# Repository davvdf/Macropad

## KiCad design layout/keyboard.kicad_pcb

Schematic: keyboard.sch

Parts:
C8: 1u; C_0805_2012Metric_Pad1.15x1.40mm_HandSolder
D_1, D_2, D_3, D_4, D_5, D_6, D_7, D_8, D_9, D_10, D_11: D; D_SOD123_axial
D_A: D; D_SOD123_axial
D_ALT: D; D_SOD123_axial
D_ASTRK: D; D_SOD123_axial
D_CAPS: D; D_SOD123_axial
D_CTRL: D; D_SOD123_axial
D_DOT: D; D_SOD123_axial
D_ENTER: D; D_SOD123_axial
D_ESC: D; D_SOD123_axial
D_L1, D_L2: D; D_SOD123_axial
D_MINUS: D; D_SOD123_axial
D_NUM: D; D_SOD123_axial
D_PLUS: D; D_SOD123_axial
D_Q: D; D_SOD123_axial
D_S: D; D_SOD123_axial
D_SHIFT: D; D_SOD123_axial
D_SLASH: D; D_SOD123_axial
D_SPACE, D_SPACE1, D_SPACE2, D_SPACE3, D_SPACE4, D_SPACE5, D_SPACE6, D_SPACE7, D_SPACE8: D; D_SOD123_axial
D_TAB: D; D_SOD123_axial
D_W: D; D_SOD123_axial
D_X: D; D_SOD123_axial
D_Z: D; D_SOD123_axial
D_`: D; D_SOD123_axial
J1: USB_mini_micro_B; USB_miniB_hirose_5S8
K_1, K_2, K_3, K_4, K_5, K_6, K_7, K_8, K_9, K_10, K_11: KEYSW; MX-1U-NoLED
K_A: KEYSW; MX-1U-NoLED
K_ALT: KEYSW; MX-1U-NoLED
K_ASTRK: KEYSW; MX-1U-NoLED
K_CAPS: KEYSW; MX-2U-NoLED
K_CTRL: KEYSW; MX-1U-NoLED
K_DOT: KEYSW; MX-1U-NoLED
K_ENTER: KEYSW; MX-1U-NoLED
K_ESC: KEYSW; MX-1U-NoLED
K_L1, K_L2: KEYSW; MX-1U-NoLED
K_MINUS: KEYSW; MX-1U-NoLED
K_NUM: KEYSW; MX-1U-NoLED
K_PLUS: KEYSW; MX-1U-NoLED
K_Q: KEYSW; MX-1U-NoLED
K_S: KEYSW; MX-1U-NoLED
K_SHIFT: KEYSW; MX-2U-NoLED
K_SLASH: KEYSW; MX-1U-NoLED
K_SPACE, K_SPACE1, K_SPACE2, K_SPACE3, K_SPACE4, K_SPACE5, K_SPACE6, K_SPACE7: KEYSW; MX-1U-NoLED
K_SPACE8: KEYSW; MX-2U-NoLED
K_TAB: KEYSW; MX-2U-NoLED
K_W: KEYSW; MX-1U-NoLED
K_X: KEYSW; MX-1U-NoLED
K_Z: KEYSW; MX-1U-NoLED
K_`: KEYSW; MX-1U-NoLED
R3: 22; R_0805_2012Metric_Pad1.15x1.40mm_HandSolder
U1: ATMEGA32U4; TQFP-44_10x10mm_P0.8mm

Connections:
/col0: K_CTRL.1, K_ESC.1, K_`.1, U1.30
/col1: K_ALT.1, K_CAPS.1, K_SHIFT.1, K_SPACE.1, K_SPACE7.1, K_TAB.1, U1.12
/col2: K_1.1, K_A.1, K_L1.1, K_Q.1, K_SPACE1.1, K_Z.1, U1.31
/col3: K_2.1, K_L2.1, K_S.1, K_SPACE2.1, K_W.1, K_X.1, U1.32
/col4: K_3.1, K_4.1, K_7.1, K_NUM.1, K_SPACE3.1, U1.18
/col5: K_5.1, K_8.1, K_10.1, K_SLASH.1, K_SPACE4.1, K_SPACE8.1, U1.19
/col6: K_6.1, K_9.1, K_11.1, K_ASTRK.1, K_DOT.1, K_SPACE5.1, U1.20
/col7: K_ENTER.1, K_MINUS.1, K_PLUS.1, K_SPACE6.1, U1.21
/row0: D_ESC.1 (K), D_SPACE.1 (K), D_SPACE1.1 (K), D_SPACE2.1 (K), D_SPACE3.1 (K), D_SPACE4.1 (K), D_SPACE5.1 (K), D_SPACE6.1 (K), U1.8
/row1: D_1.1 (K), D_2.1 (K), D_ASTRK.1 (K), D_MINUS.1 (K), D_NUM.1 (K), D_SLASH.1 (K), D_SPACE7.1 (K), D_`.1 (K), U1.9
/row2: D_7.1 (K), D_8.1 (K), D_9.1 (K), D_Q.1 (K), D_TAB.1 (K), D_W.1 (K), U1.10
/row3: D_4.1 (K), D_5.1 (K), D_6.1 (K), D_A.1 (K), D_CAPS.1 (K), D_PLUS.1 (K), D_S.1 (K), U1.11
/row4: D_3.1 (K), D_10.1 (K), D_11.1 (K), D_SHIFT.1 (K), D_X.1 (K), D_Z.1 (K), U1.28
/row5: D_ALT.1 (K), D_CTRL.1 (K), D_DOT.1 (K), D_ENTER.1 (K), D_L1.1 (K), D_L2.1 (K), D_SPACE8.1 (K), U1.29
GND: U1.5, U1.15, U1.23; also elsewhere on the board
unnamed 15: U1.16; also elsewhere on the board
unnamed 16: U1.17; also elsewhere on the board
unnamed 17: U1.6; also elsewhere on the board
unnamed: D_1.2 (A), K_1.2
unnamed: D_2.2 (A), K_2.2
unnamed: D_3.2 (A), K_3.2
unnamed: D_4.2 (A), K_4.2
unnamed: D_5.2 (A), K_5.2
unnamed: D_6.2 (A), K_6.2
unnamed: D_7.2 (A), K_7.2
unnamed: D_8.2 (A), K_8.2
unnamed: D_9.2 (A), K_9.2
unnamed: D_10.2 (A), K_10.2
unnamed: D_11.2 (A), K_11.2
unnamed: D_A.2 (A), K_A.2
unnamed: D_ALT.2 (A), K_ALT.2
unnamed: D_ASTRK.2 (A), K_ASTRK.2
unnamed: D_CAPS.2 (A), K_CAPS.2
unnamed: D_CTRL.2 (A), K_CTRL.2
unnamed: D_DOT.2 (A), K_DOT.2
unnamed: D_ENTER.2 (A), K_ENTER.2
unnamed: D_ESC.2 (A), K_ESC.2
unnamed: D_L1.2 (A), K_L1.2
unnamed: D_L2.2 (A), K_L2.2
unnamed: D_MINUS.2 (A), K_MINUS.2
unnamed: D_NUM.2 (A), K_NUM.2
unnamed: D_PLUS.2 (A), K_PLUS.2
unnamed: D_Q.2 (A), K_Q.2
unnamed: D_S.2 (A), K_S.2
unnamed: D_SHIFT.2 (A), K_SHIFT.2
unnamed: D_SLASH.2 (A), K_SLASH.2
unnamed: D_SPACE1.2 (A), K_SPACE1.2
unnamed: D_SPACE2.2 (A), K_SPACE2.2
unnamed: D_SPACE3.2 (A), K_SPACE3.2
unnamed: D_SPACE4.2 (A), K_SPACE4.2
unnamed: D_SPACE5.2 (A), K_SPACE5.2
unnamed: D_SPACE6.2 (A), K_SPACE6.2
unnamed: D_SPACE7.2 (A), K_SPACE7.2
unnamed: D_SPACE8.2 (A), K_SPACE8.2
unnamed: D_SPACE.2 (A), K_SPACE.2
unnamed: D_TAB.2 (A), K_TAB.2
unnamed: D_W.2 (A), K_W.2
unnamed: D_X.2 (A), K_X.2
unnamed: D_Z.2 (A), K_Z.2
unnamed: D_`.2 (A), K_`.2
unnamed 60: U1.13; also elsewhere on the board
unnamed 61: U1.33; also elsewhere on the board
unnamed: R3.1, U1.3
unnamed 63: U1.4; also elsewhere on the board
unnamed 80: R3.2; also elsewhere on the board
VCC: U1.2, U1.14, U1.24; also elsewhere on the board

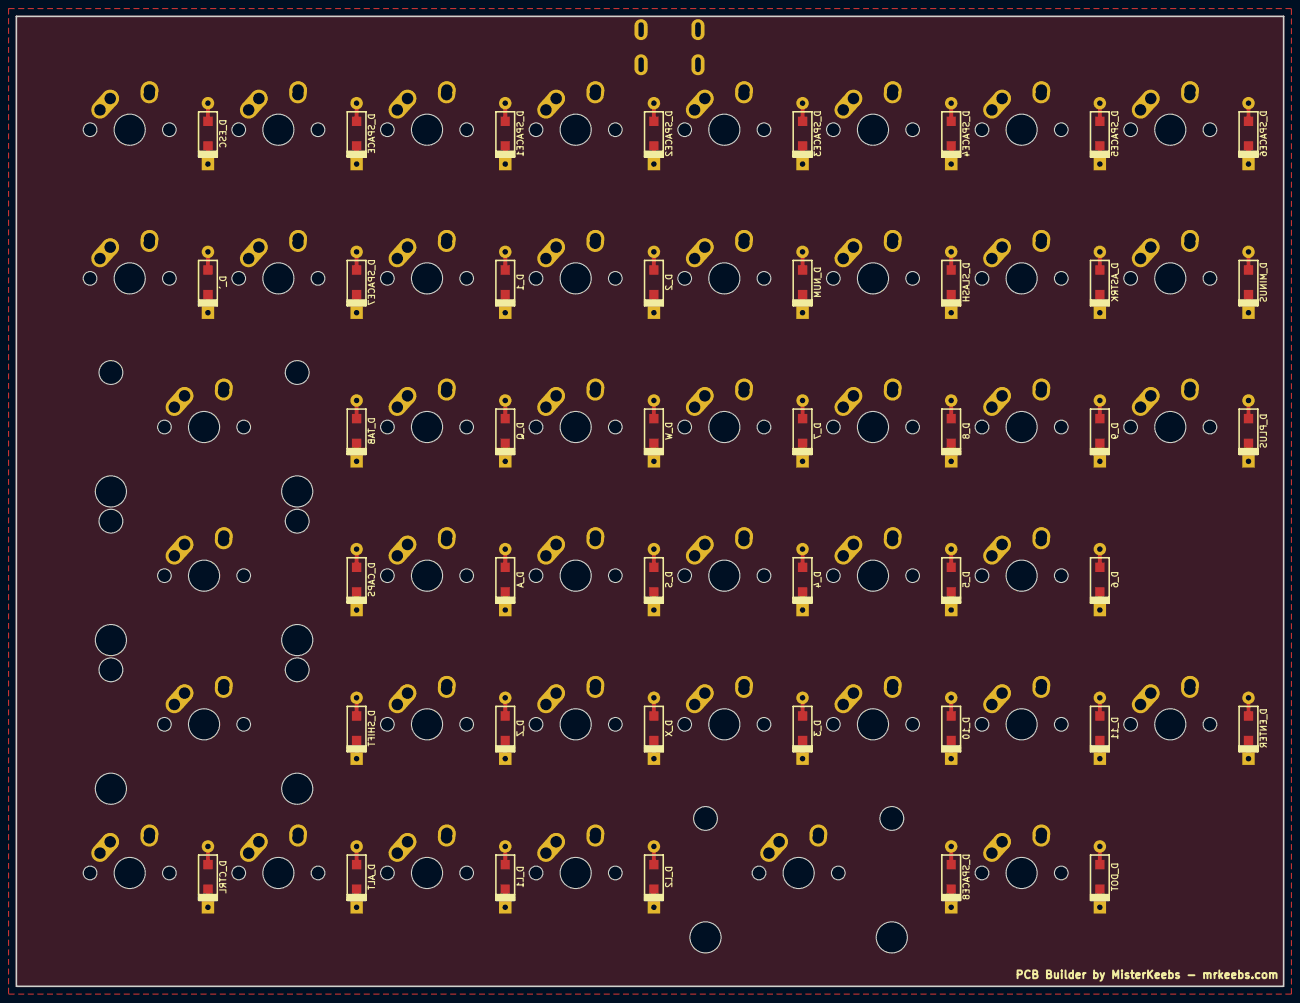
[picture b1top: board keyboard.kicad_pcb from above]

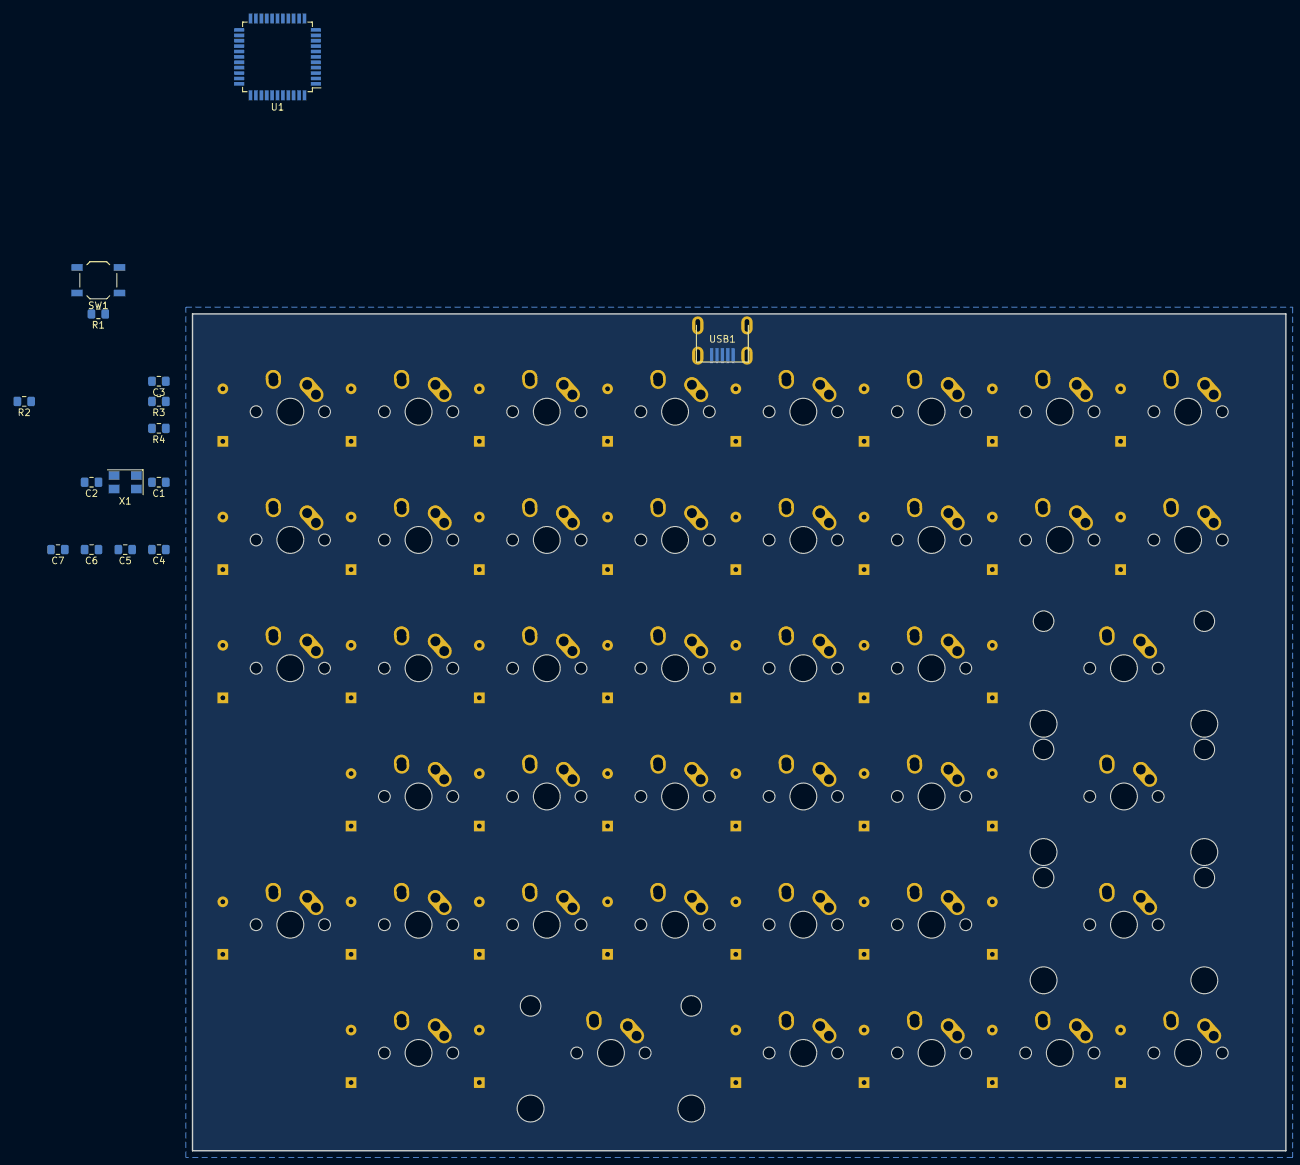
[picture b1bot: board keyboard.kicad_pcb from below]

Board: 2 copper layers, 162.4 x 124.3 mm, 99 parts (15 on the bottom side), 67 nets, no tracks yet.

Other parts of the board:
C1, C2, C3, C4, C5, C6, C7: 22pF; C_0805_2012Metric_Pad1.15x1.40mm_HandSolder
R1, R2: 10k; R_0805_2012Metric_Pad1.15x1.40mm_HandSolder
R4: 22; R_0805_2012Metric_Pad1.15x1.40mm_HandSolder
SW1: SW_PUSH; SW_SPST_TL3342
USB1: Molex-0548190589; Molex-0548190589-Assembly
X1: XTAL_GND; Crystal_SMD_5032-4Pin_5.0x3.2mm

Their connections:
GND: C1.2, C2.2, C3.2, C4.2, C5.2, C6.2, C7.2, R2.2, SW1.1, USB1.1, X1.2, X1.4; also elsewhere on the board
unnamed 15: C1.1, X1.1; also elsewhere on the board
unnamed 16: C2.1, X1.3; also elsewhere on the board
unnamed 17: C3.1; also elsewhere on the board
unnamed 60: R1.1, SW1.2; also elsewhere on the board
unnamed 61: R2.1; also elsewhere on the board
unnamed 63: R4.1; also elsewhere on the board
unnamed 80: USB1.2; also elsewhere on the board
unnamed: R4.2, USB1.3
VCC: C4.1, C5.1, C6.1, C7.1, R1.2, USB1.5; also elsewhere on the board

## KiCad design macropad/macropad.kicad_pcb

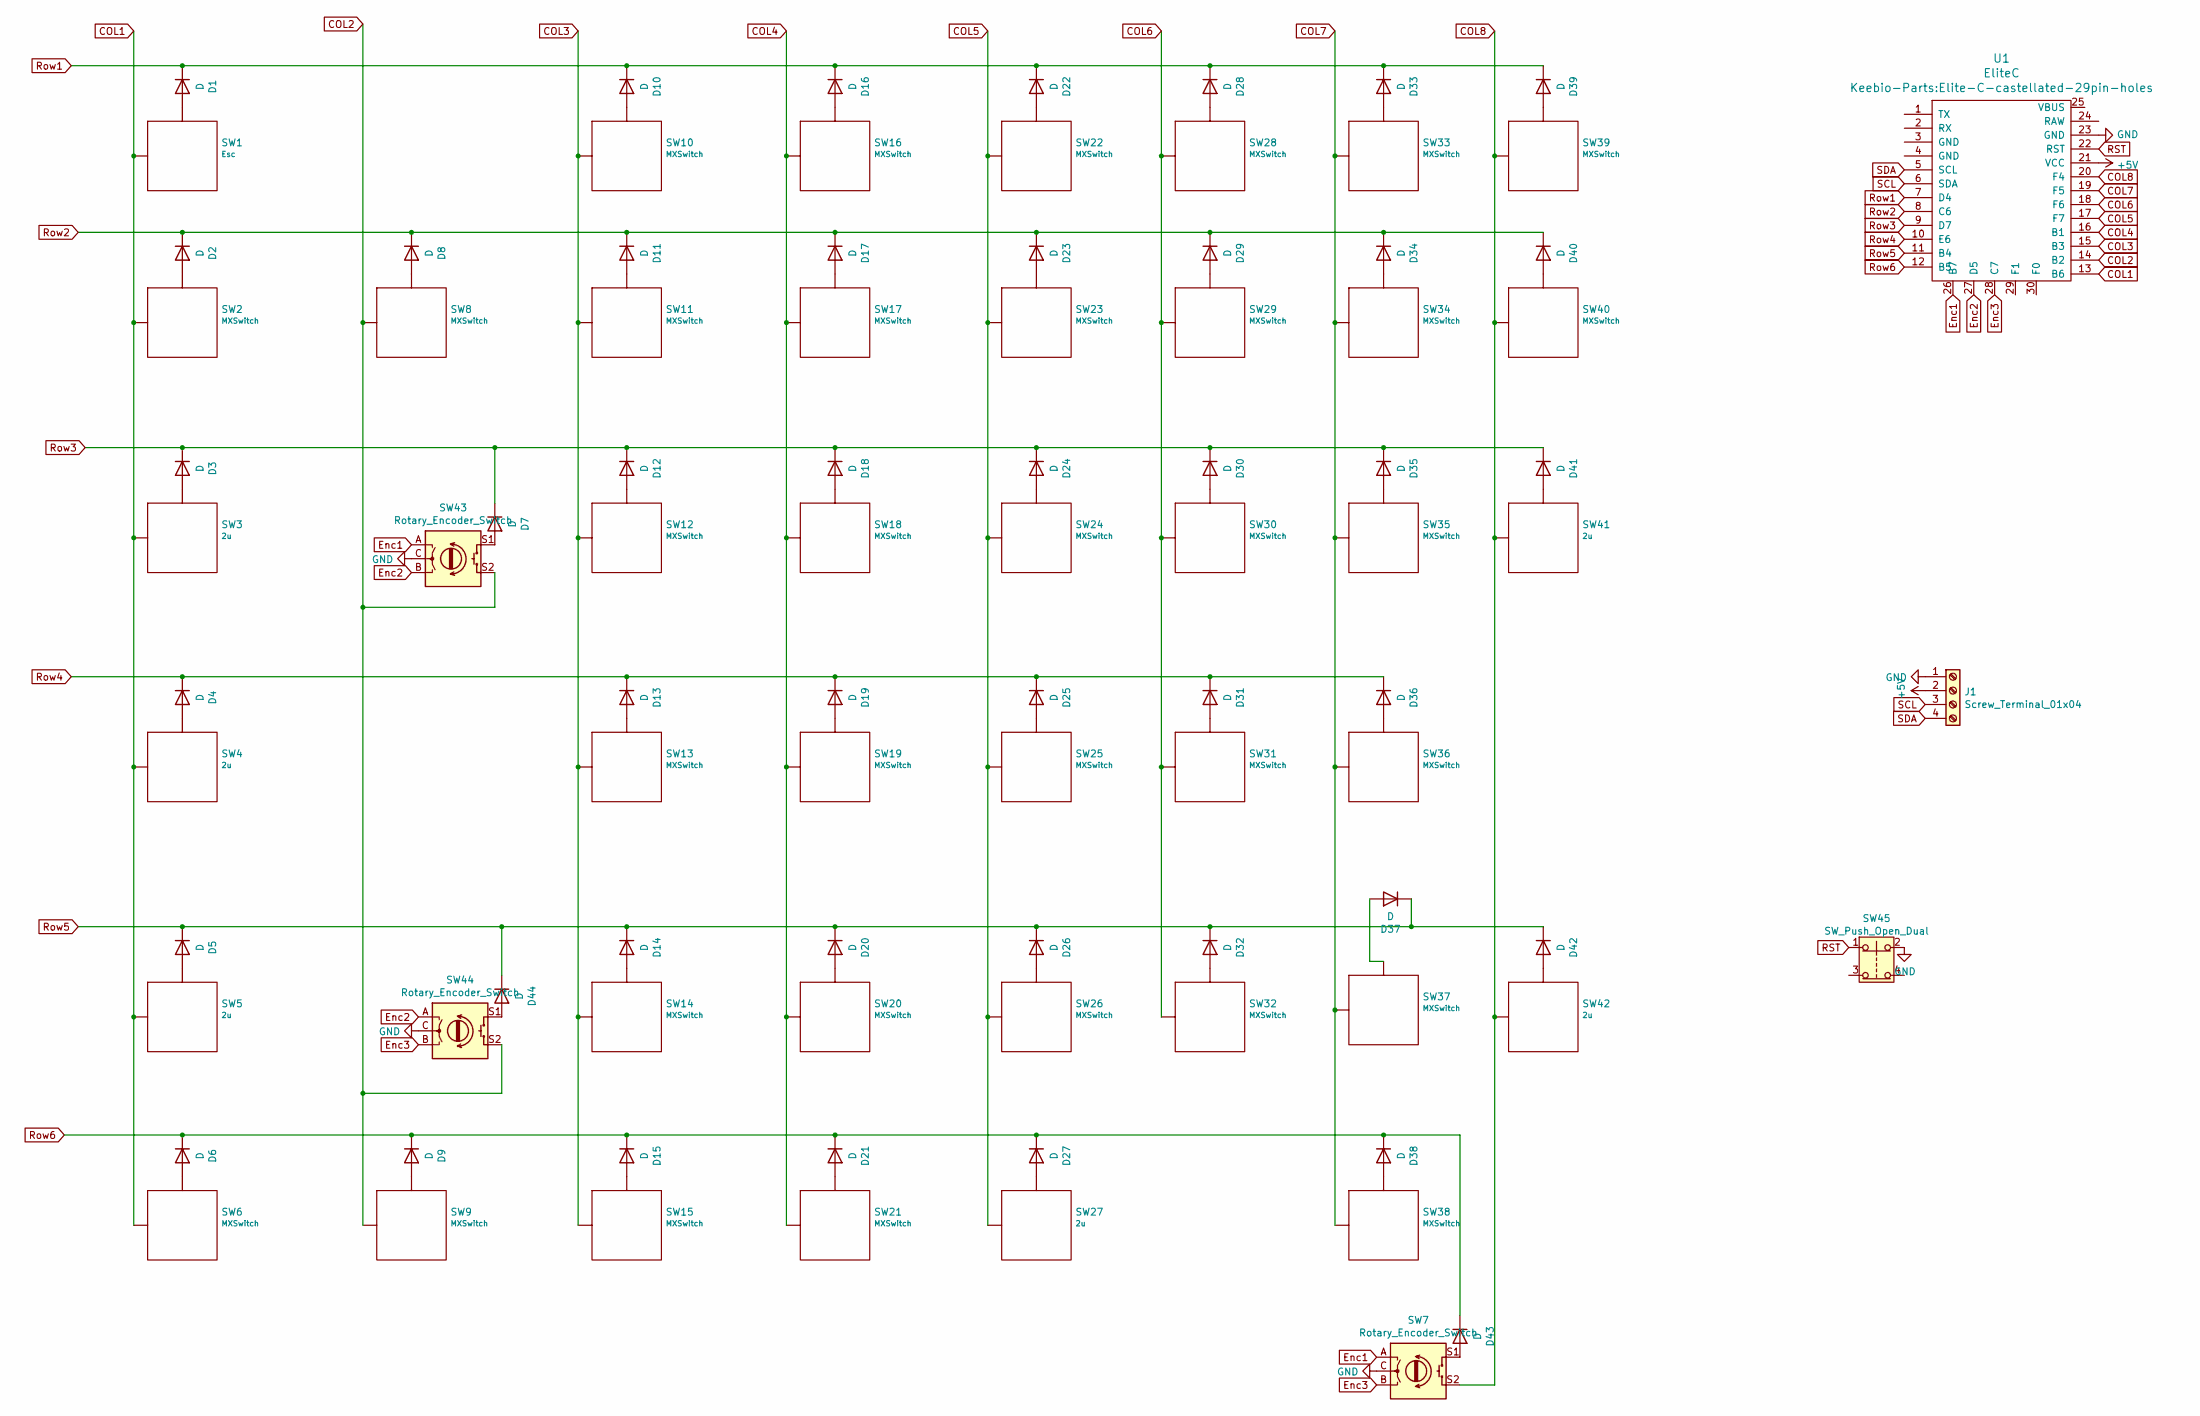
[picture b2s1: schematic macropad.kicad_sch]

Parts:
D1, D2, D3, D4, D5, D6, D7, D8, D9, D10, D11, D12, D13, D14, D15, D16, D17, D18, D19, D20, D21, D22, D23, D24, D25, D26, D27, D28, D29, D30, D31, D32, D33, D34, D35, D36, D37, D38, D39, D40, D41, D42, D43, D44: D; D_SOD-123
J1: Screw_Terminal_01x04; PinHeader_1x04_P2.54mm_Vertical
SW1: Esc; SW_Hotswap_Kailh_1.00u
SW2, SW6, SW8, SW9, SW10, SW11, SW12, SW13, SW14, SW15, SW16, SW17, SW18, SW19, SW20, SW21, SW22, SW23, SW24, SW25, SW26, SW28, SW29, SW30, SW31, SW32, SW33, SW34, SW35, SW36, SW37, SW38, SW39, SW40: MXSwitch; SW_Hotswap_Kailh_1.00u
SW3, SW5, SW27: 2u; MXOnly-2U-Hotswap
SW4: 2u; MXOnly-1.75U-Hotswap
SW7, SW43, SW44: Rotary_Encoder_Switch; RotaryEncoder_Alps_EC11E-Switch_Vertical_H20mm
SW41, SW42: 2u; 2u_Hotswap_Vertical
SW45: SW_Push_Open_Dual; SW_PUSH_6mm
U1: EliteC; Elite-C-castellated-29pin-holes

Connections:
+5V: J1.2, U1.21 (VCC)
COL1: SW1.1 (Col), SW2.1 (Col), SW3.1 (Col), SW4.1 (Col), SW5.1 (Col), SW6.1 (Col), U1.13 (B6)
COL2: SW8.1 (Col), SW9.1 (Col), SW43.S2, SW44.S2, U1.14 (B2)
COL3: SW10.1 (Col), SW11.1 (Col), SW12.1 (Col), SW13.1 (Col), SW14.1 (Col), SW15.1 (Col), U1.15 (B3)
COL4: SW16.1 (Col), SW17.1 (Col), SW18.1 (Col), SW19.1 (Col), SW20.1 (Col), SW21.1 (Col), U1.16 (B1)
COL5: SW22.1 (Col), SW23.1 (Col), SW24.1 (Col), SW25.1 (Col), SW26.1 (Col), SW27.1 (Col), U1.17 (F7)
COL6: SW28.1 (Col), SW29.1 (Col), SW30.1 (Col), SW31.1 (Col), SW32.1 (Col), U1.18 (F6)
COL7: SW33.1 (Col), SW34.1 (Col), SW35.1 (Col), SW36.1 (Col), SW37.1 (Col), SW38.1 (Col), U1.19 (F5)
COL8: SW7.S2, SW39.1 (Col), SW40.1 (Col), SW41.1 (Col), SW42.1 (Col), U1.20 (F4)
Enc1: SW7.A, SW43.A, U1.26 (B7)
Enc2: SW43.B, SW44.A, U1.27 (D5)
Enc3: SW7.B, SW44.B, U1.28 (C7)
GND: J1.1, SW7.C, SW43.C, SW44.C, SW45.2, U1.23 (GND)
unnamed: D1.2 (A), SW1.2 (Row)
unnamed: D2.2 (A), SW2.2 (Row)
unnamed: D3.2 (A), SW3.2 (Row)
unnamed: D4.2 (A), SW4.2 (Row)
unnamed: D5.2 (A), SW5.2 (Row)
unnamed: D6.2 (A), SW6.2 (Row)
unnamed: D7.2 (A), SW43.S1
unnamed: D8.2 (A), SW8.2 (Row)
unnamed: D9.2 (A), SW9.2 (Row)
unnamed: D10.2 (A), SW10.2 (Row)
unnamed: D11.2 (A), SW11.2 (Row)
unnamed: D12.2 (A), SW12.2 (Row)
unnamed: D13.2 (A), SW13.2 (Row)
unnamed: D14.2 (A), SW14.2 (Row)
unnamed: D15.2 (A), SW15.2 (Row)
unnamed: D16.2 (A), SW16.2 (Row)
unnamed: D17.2 (A), SW17.2 (Row)
unnamed: D18.2 (A), SW18.2 (Row)
unnamed: D19.2 (A), SW19.2 (Row)
unnamed: D20.2 (A), SW20.2 (Row)
unnamed: D21.2 (A), SW21.2 (Row)
unnamed: D22.2 (A), SW22.2 (Row)
unnamed: D23.2 (A), SW23.2 (Row)
unnamed: D24.2 (A), SW24.2 (Row)
unnamed: D25.2 (A), SW25.2 (Row)
unnamed: D26.2 (A), SW26.2 (Row)
unnamed: D27.2 (A), SW27.2 (Row)
unnamed: D28.2 (A), SW28.2 (Row)
unnamed: D29.2 (A), SW29.2 (Row)
unnamed: D30.2 (A), SW30.2 (Row)
unnamed: D31.2 (A), SW31.2 (Row)
unnamed: D32.2 (A), SW32.2 (Row)
unnamed: D33.2 (A), SW33.2 (Row)
unnamed: D34.2 (A), SW34.2 (Row)
unnamed: D35.2 (A), SW35.2 (Row)
unnamed: D36.2 (A), SW36.2 (Row)
unnamed: D37.2 (A), SW37.2 (Row)
unnamed: D38.2 (A), SW38.2 (Row)
unnamed: D39.2 (A), SW39.2 (Row)
unnamed: D40.2 (A), SW40.2 (Row)
unnamed: D41.2 (A), SW41.2 (Row)
unnamed: D42.2 (A), SW42.2 (Row)
unnamed: D43.2 (A), SW7.S1
unnamed: D44.2 (A), SW44.S1
RST: SW45.1, U1.22 (RST)
Row1: D1.1 (K), D10.1 (K), D16.1 (K), D22.1 (K), D28.1 (K), D33.1 (K), D39.1 (K), U1.7 (D4)
Row2: D2.1 (K), D8.1 (K), D11.1 (K), D17.1 (K), D23.1 (K), D29.1 (K), D34.1 (K), D40.1 (K), U1.8 (C6)
Row3: D3.1 (K), D7.1 (K), D12.1 (K), D18.1 (K), D24.1 (K), D30.1 (K), D35.1 (K), D41.1 (K), U1.9 (D7)
Row4: D4.1 (K), D13.1 (K), D19.1 (K), D25.1 (K), D31.1 (K), D36.1 (K), U1.10 (E6)
Row5: D5.1 (K), D14.1 (K), D20.1 (K), D26.1 (K), D32.1 (K), D37.1 (K), D42.1 (K), D44.1 (K), U1.11 (B4)
Row6: D6.1 (K), D9.1 (K), D15.1 (K), D21.1 (K), D27.1 (K), D38.1 (K), D43.1 (K), U1.12 (B5)
SCL: J1.3, U1.6 (SDA)
SDA: J1.4, U1.5 (SCL)

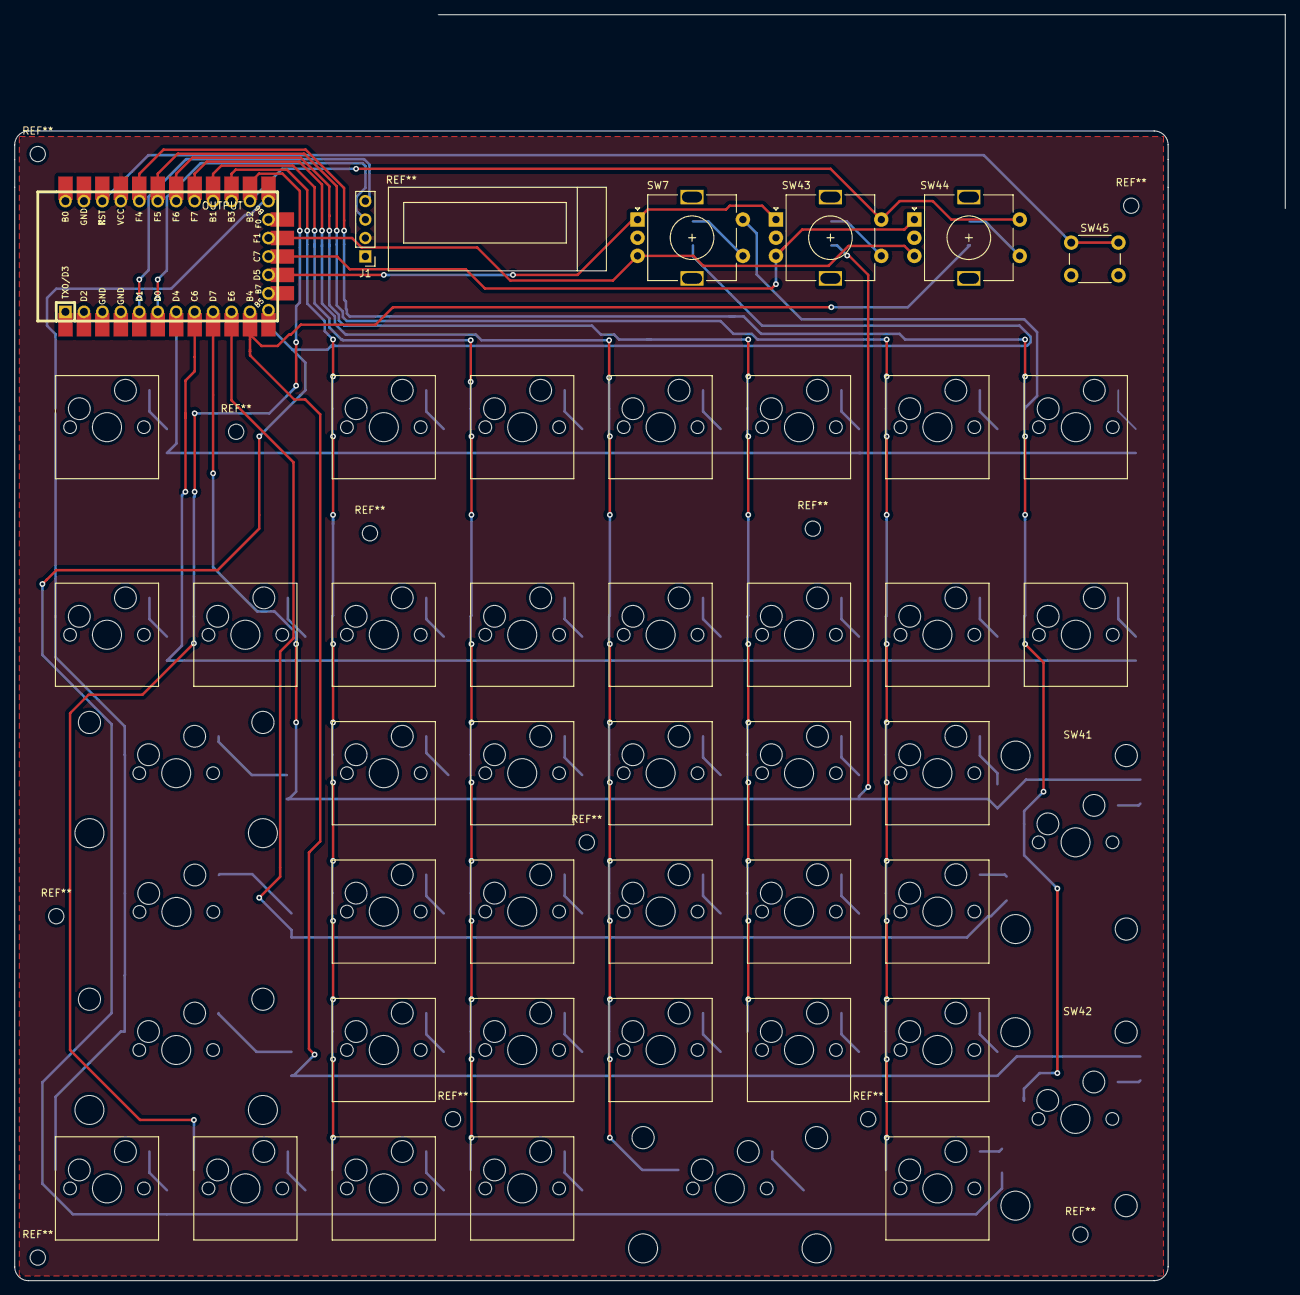
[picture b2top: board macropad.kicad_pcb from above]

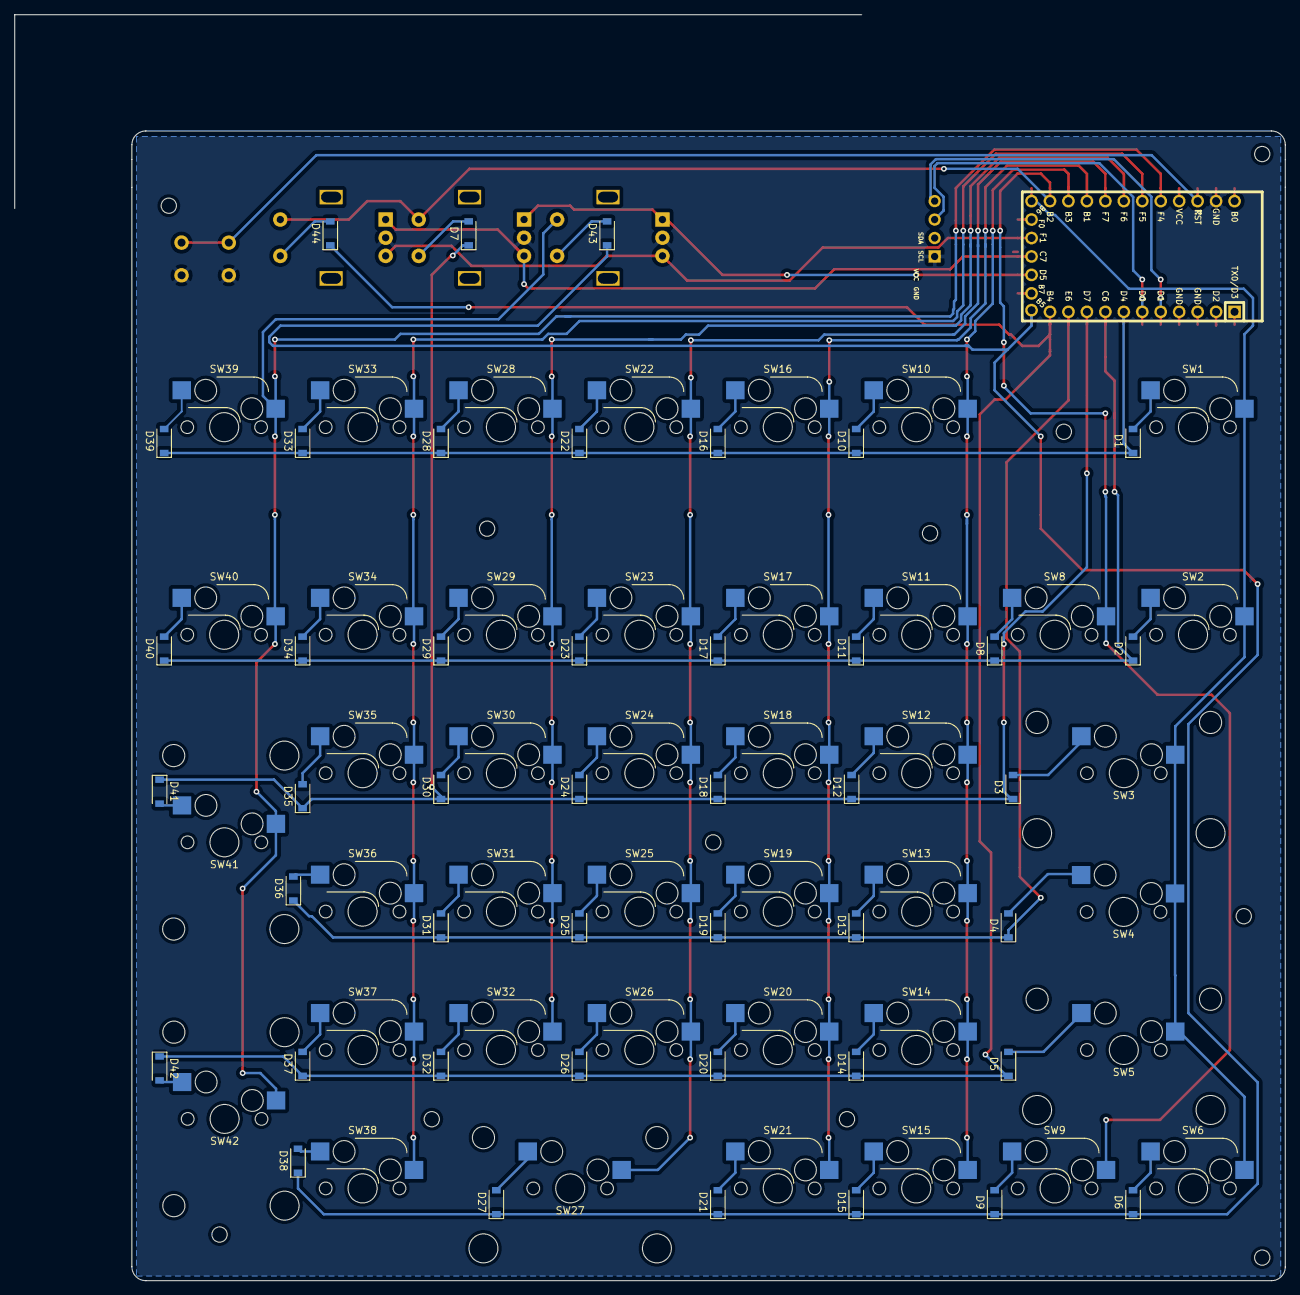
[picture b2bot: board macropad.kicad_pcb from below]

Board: 2 copper layers, 158.8 x 158.2 mm, 91 parts (44 on the bottom side), 66 nets.
